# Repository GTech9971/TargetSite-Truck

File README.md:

# TargetSite-Truck

 ionic/react iosからBlueooth経由でデータを受信し、モータを操作することでラジコンを動かす

## マイコン PIC16F1827

[datasheet](datasheet/pic16f1827.pdf)

## HM-10

BLE規格のモジュール

| サービスUUID | キャラUUID |
| ------------ | ---------- |
| FFE0         | FFE1       |

[datasheet](datasheet/DSD%20TECH%20HM-10%20datasheet.pdf)

### USART

RX = RB1
TX = RB2

ピンを全てデジタルに設定

```
ANSELA = 0x00;
ANSELB = 0x00;
```

RXピンを入力モードに設定

```
TRISA = 0x00;
TRISB = 0x02;
```

RX,TXを有効化

```
TXSTA = 0x20;
RCSTA = 0x90;
```

通信設定

```
//16bit
BAUDCON = 0x08;

//9600bit mode
SPBGR = 51;
```

データ送信

```
void send(unsigned char data){
    while(!TXSTAbits.TRMT);
    TXREG = data;
}

```

### 割り込み

割り込み有効化

```
//interrupt flg clear
PIR1bits.RCIF = 0;
    
//USART recive interrupt enable
PIE1bits.RCIE = 1;
//peripheral enable
PEIE = 1;
//global enable
GIE = 1;
```

割り込み関数

```
void __interrupt() isr(void){
    if(PIR1bits.RCIF){
        //flg clear
        PIR1bits.RCIF = 0;
        //error
        if((RCSTAbits.OERR) || (RCSTAbits.FERR)){
            RCSTA = 0;
            RCSTA = 0x90;
        }else{
        //not error            
            //RCREGが受信データ
            send(RCREG);
        }
    }
}
```

## TA7291P

モータードライバー
[datasheet](datasheet/ta7291.pdf)

### ファンクション

| IN1 | IN2 | モード   |
| --- | --- | -------- |
| 0   | 0   | ストップ |
| 1   | 0   | 前進     |
| 0   | 1   | 後退     |
| 1   | 1   | ブレーキ |

### CCP(PWMモード)

PWM有効化 CCP3

```
//pwm initialize
// CCP3M PWM; DC3B 3; 
CCP3CON = 0x3C;    
// CCPR3L 127; 
CCPR3L = 0x7F;    
// CCPR3H 0; 
CCPR3H = 0x00;    
// Selecting Timer 2
CCPTMRS0bits.C3TSEL = 0x0;
    
//timer2 initialize
// PR2 255; 
PR2 = 0xFF;
// TMR2 0; 
TMR2 = 0x00;
// Clearing IF flag.
PIR1bits.TMR2IF = 0;
// T2CKPS 1:1; T2OUTPS 1:1; TMR2ON on; 
T2CON = 0x04;
```

## データ仕様

| bit7 | bit6 | bit5 |  bit4   | bit3 | bit2 | bit1 | bit0 |
| :--: | :--: | :--: | :-----: | :--: | :--: | :--: | :--: |
|  >   | CMD  |  >   | INC/DEC |  >   | SPD  |      |      |

### CMD

トラックへの命令
| bit7 | bit6 |  モード  |
| :--: | :--: | :------: |
|  0   |  0   |   停止   |
|  1   |  0   |   前進   |
|  0   |  1   |   後退   |
|  1   |  1   | ブレーキ |

### INC/DEC

- INC

    現在のスピードからSPDの値に増加していく

- DEC
    現在のスピードから徐々に減少していく

| bit5 | bit4 | モード |
| :--: | :--: | :----: |
|  0   |  0   |  通常  |
|  0   |  1   |  INC   |
|  1   |  0   |  DEC   |

### SPD

モーターのスピードを設定する(10進数で0~10までの値)
| bit3 | bit2 | bit1 | bit0 |
| ---- | ---- | ---- | ---- |

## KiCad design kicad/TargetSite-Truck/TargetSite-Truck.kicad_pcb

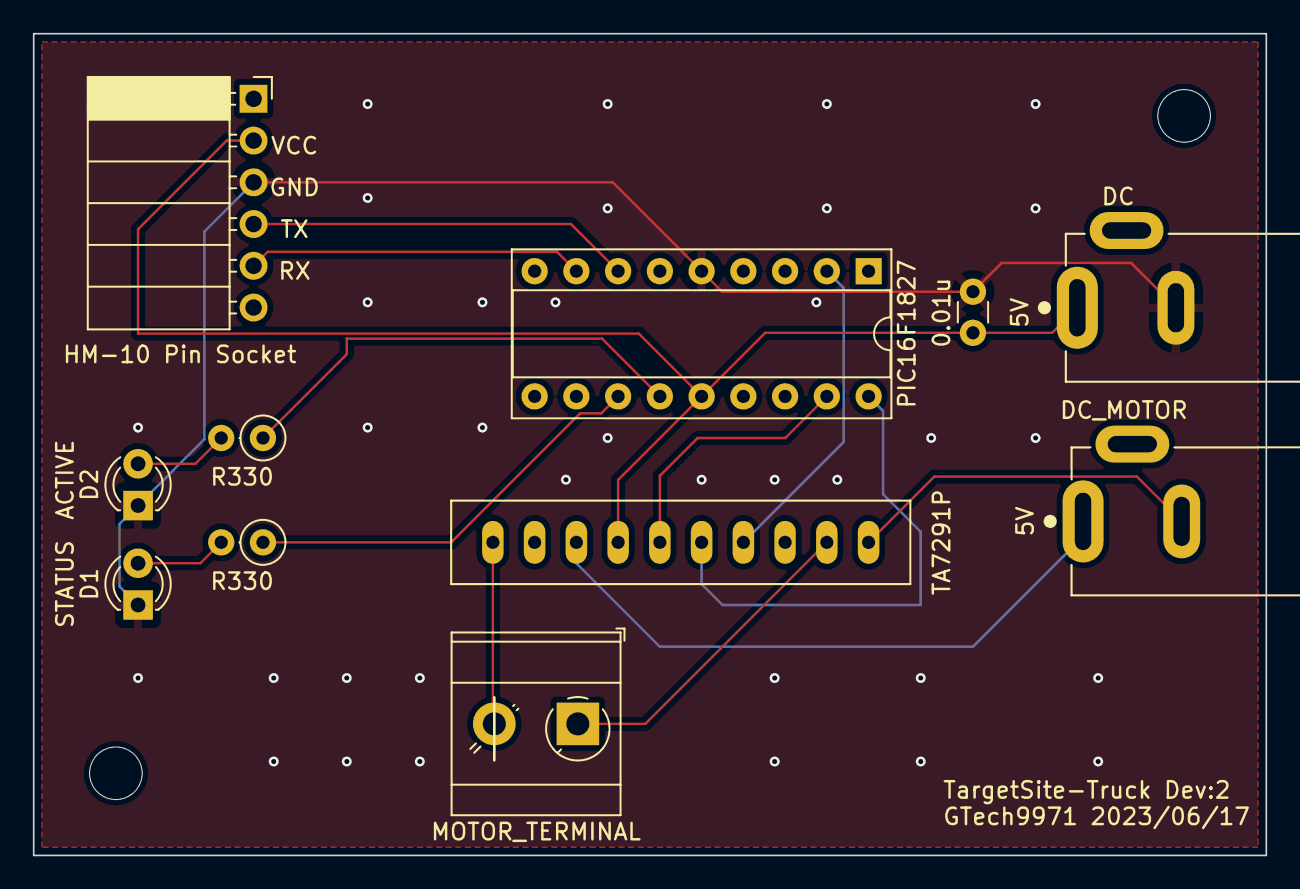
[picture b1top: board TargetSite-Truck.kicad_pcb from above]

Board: 2 copper layers, 75.0 x 50.0 mm, 13 parts (0 on the bottom side), 15 nets.

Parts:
0.01u: 0.01u; C_Disc_D3.0mm_W1.6mm_P2.50mm
D1: LED_STATUS; LED_D3.0mm
D2: LED_ACTIVATE; LED_D3.0mm
DC: 5v; CUI_PJ-002AH
DC_MOTOR: 9v; CUI_PJ-002AH
HM-10 Pin Socket: HM10; PinSocket_1x06_P2.54mm_Horizontal
MH1, MH2: MountingHole_3.2mm_M3
MOTOR_TERMINAL: Motor_DC; TerminalBlock_MetzConnect_Type073_RT02602HBLU_1x02_P5.08mm_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
PIC16F1827: PIC16F1827-E/P; DIP-18_W7.62mm_Socket
R330, R330#2: R330; R_Axial_DIN0207_L6.3mm_D2.5mm_P2.54mm_Vertical
TA7291P: TA7291P; HSIP10

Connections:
DC_GND: DC_MOTOR.2, TA7291P.1 (GND)
DC_VCC: DC_MOTOR.1, TA7291P.8 (VS)
Driver_IN1: PIC16F1827.18 (RA1/AN1/CPS1/C12IN1-/~SS2), TA7291P.5 (IN1)
Driver_IN2: PIC16F1827.17 (RA0/AN0/CPS0/C12IN0-/SDO2), TA7291P.6 (IN2)
Driver_Ref: PIC16F1827.2 (RA3/AN3/CPS3/C12IN3-/C1IN+/VREF+/C1OUT/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), TA7291P.4 (VREF)
GND: 0.01u.1, D1.1 (K), D2.1 (K), DC.2, HM-10 Pin Socket.3, PIC16F1827.5 (VSS)
HM10_RX: HM-10 Pin Socket.5, PIC16F1827.8 (RB2/AN10/CPS10/MDMIN/TX/CK/RX/DT/SDA2/S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)
HM10_TX: HM-10 Pin Socket.4, PIC16F1827.7 (RB1/AN11/CPS11/RX/DT/SDA1/SDI1)
Motor_IN1: MOTOR_TERMINAL.1 (+), TA7291P.2 (OUT1)
Motor_IN2: MOTOR_TERMINAL.2 (-), TA7291P.10 (OUT2)
unnamed: D1.2 (A), R330.2
unnamed: D2.2 (A), R330#2.2
unnamed: PIC16F1827.12 (RB6/AN5/CPS5/T1CKI/T1OSI/P1C/CCP2/P2A/I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), R330.1
unnamed: PIC16F1827.13 (RB7/AN6/CPS6/T1OSO/P1D/P2B/MDCIN1/ICSPD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), R330#2.1
VCC: 0.01u.2, DC.1, HM-10 Pin Socket.2, PIC16F1827.14 (VDD), TA7291P.7 (VCC)

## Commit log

2023-05-06 回路図、フットプリント作成
2023-05-07 プログラムプロジェクトを追加
2023-05-26 回路図の作成、PCBの作成
2023-05-27 ガーバーデータの作成
2023-06-06 データ仕様を記載
2023-06-06 データシートの追加 データ仕様の修正
2023-06-06 ドライバーコードを実装 Ledを実装 HM10の初期化を実装 トラックコマンドを実装
2023-06-07 コマンドの処理をいくつか実装 エラーが出る状態
2023-06-09 プログラムのバグを修正 デバックモードでテスト実施
2023-06-10 ドライバーのピンアサインを修正 PWM、Timerの初期化を忘れていたのでドライバーの初期化時に設定
2023-06-11 発注した基板でモータが動作したことを確認。 動かなかった原因は以下 PWM・タイマー2の有効化ができていなかった。 電源起動時に入力1,2をLにしていなかった。 forward関数にバグがあった。テストプロジェクトもバグがあるので動作しない。
2023-06-17 回路基板設計修正
    RA0、RA1の配線を引き直した
    ターミナルのピッチサイズを5.08mmに変更
2023-07-03 pwm制御をオフにした
2023-07-10 不要なbkupフォルダを管理対象から削除
2023-07-10 backupsを管理対象から削除
